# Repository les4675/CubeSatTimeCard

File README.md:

Currently we have developed models from the top level overview of our time card, along with setting up the SOM. Our goal in the next few months is program the SOM to take in data from a GNSS through the CAN protcol and to fine tone the PLL with the atomic clock that we have aquired.

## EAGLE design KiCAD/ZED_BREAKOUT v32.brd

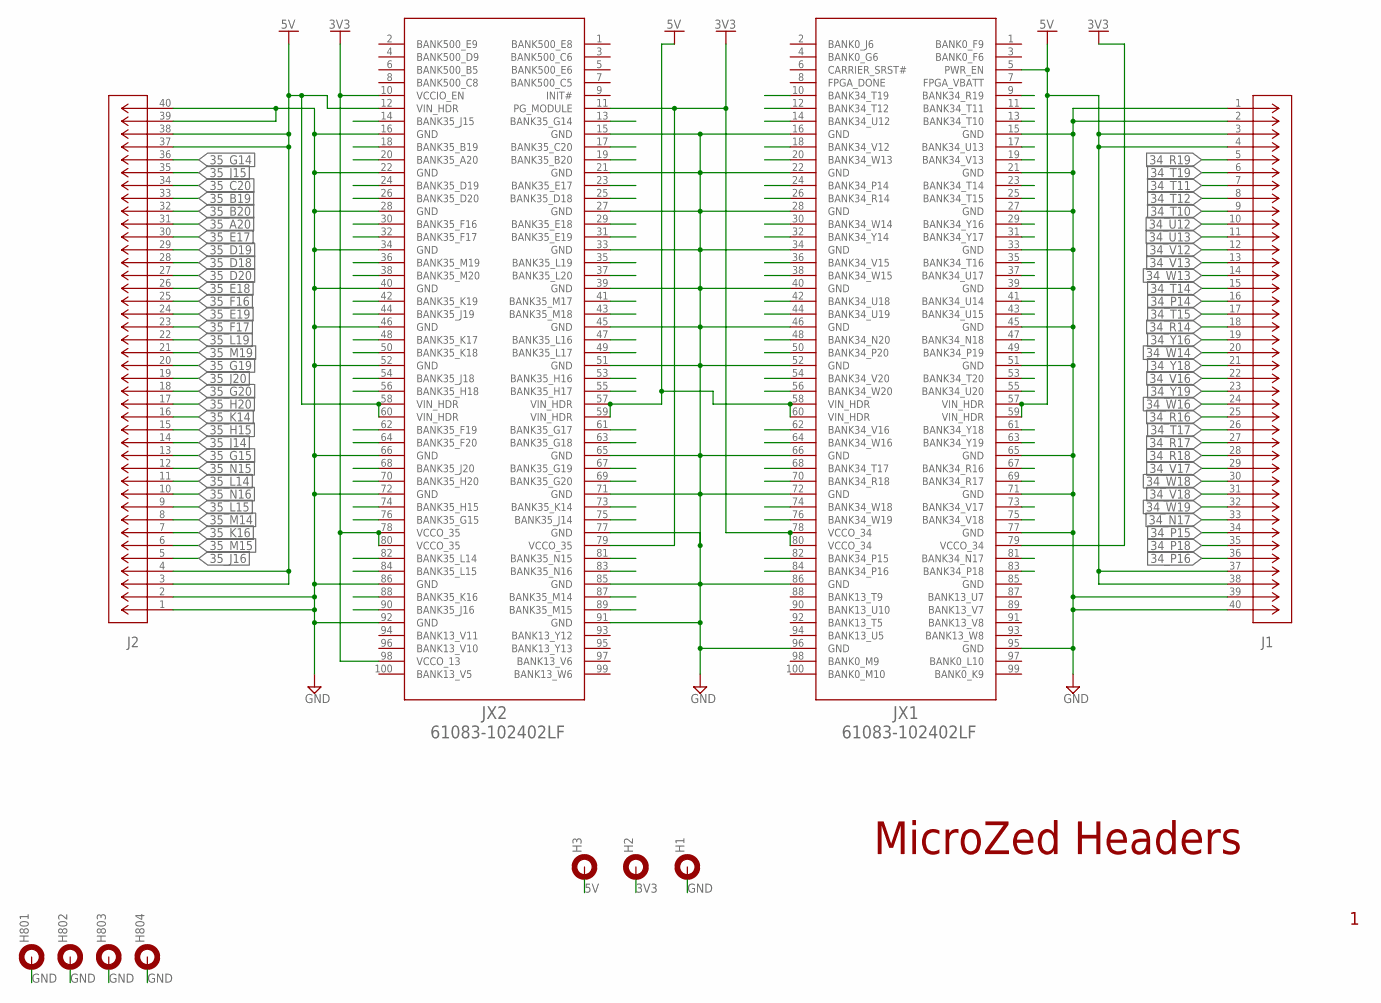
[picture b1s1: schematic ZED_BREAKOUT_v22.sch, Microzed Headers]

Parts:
H1, H2, H3, H801, H802, H803, H804: MOUNT-PAD-ROUND5.0; 5,0-PAD
J1, J2: TD-120-G-AACON40_2X20_TU_HTS_SAI; CON40_2X20_TU_HTS_SAI
JX1, JX2: 61083-102402LF

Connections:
3V3: H2.B5, JX1.78 (VCCO_34), JX1.79 (VCCO_34), JX1.80 (VCCO_34), JX2.10 (VCCIO_EN), JX2.11 (PG_MODULE), JX2.78 (VCCO_35), JX2.79 (VCCO_35), JX2.80 (VCCO_35), JX2.98 (VCCO_13)
5V: H3.B5, J1.3, J1.4, J1.37, J1.38, J2.3, J2.4, J2.37, J2.38, JX1.5 (PWR_EN), JX1.57 (VIN_HDR), JX1.58 (VIN_HDR), JX1.59 (VIN_HDR), JX1.60 (VIN_HDR), JX2.12 (VIN_HDR), JX2.57 (VIN_HDR), JX2.58 (VIN_HDR), JX2.59 (VIN_HDR), JX2.60 (VIN_HDR)
34_N17: J1.33, JX1.81 (BANK34_N17)
34_N18: JX1.47 (BANK34_N18)
34_N20: JX1.48 (BANK34_N20)
34_P14: J1.16, JX1.24 (BANK34_P14)
34_P15: J1.34, JX1.82 (BANK34_P15)
34_P16: J1.36, JX1.84 (BANK34_P16)
34_P18: J1.35, JX1.83 (BANK34_P18)
34_P19: JX1.49 (BANK34_P19)
34_P20: JX1.50 (BANK34_P20)
34_R14: J1.18, JX1.26 (BANK34_R14)
34_R16: J1.25, JX1.67 (BANK34_R16)
34_R17: J1.27, JX1.69 (BANK34_R17)
34_R18: J1.28, JX1.70 (BANK34_R18)
34_R19: J1.5, JX1.9 (BANK34_R19)
34_T10: J1.9, JX1.13 (BANK34_T10)
34_T11: J1.7, JX1.11 (BANK34_T11)
34_T12: J1.8, JX1.12 (BANK34_T12)
34_T14: J1.15, JX1.23 (BANK34_T14)
34_T15: J1.17, JX1.25 (BANK34_T15)
34_T16: JX1.35 (BANK34_T16)
34_T17: J1.26, JX1.68 (BANK34_T17)
34_T19: J1.6, JX1.10 (BANK34_T19)
34_T20: JX1.53 (BANK34_T20)
34_U12: J1.10, JX1.14 (BANK34_U12)
34_U13: J1.11, JX1.17 (BANK34_U13)
34_U14: JX1.41 (BANK34_U14)
34_U15: JX1.43 (BANK34_U15)
34_U17: JX1.37 (BANK34_U17)
34_U18: JX1.42 (BANK34_U18)
34_U19: JX1.44 (BANK34_U19)
34_U20: JX1.55 (BANK34_U20)
34_V12: J1.12, JX1.18 (BANK34_V12)
34_V13: J1.13, JX1.19 (BANK34_V13)
34_V15: JX1.36 (BANK34_V15)
34_V16: J1.22, JX1.62 (BANK34_V16)
34_V17: J1.29, JX1.73 (BANK34_V17)
34_V18: J1.31, JX1.75 (BANK34_V18)
34_V20: JX1.54 (BANK34_V20)
34_W13: J1.14, JX1.20 (BANK34_W13)
34_W14: J1.20, JX1.30 (BANK34_W14)
34_W15: JX1.38 (BANK34_W15)
34_W16: J1.24, JX1.64 (BANK34_W16)
34_W18: J1.30, JX1.74 (BANK34_W18)
34_W19: J1.32, JX1.76 (BANK34_W19)
34_W20: JX1.56 (BANK34_W20)
34_Y14: JX1.32 (BANK34_Y14)
34_Y16: J1.19, JX1.29 (BANK34_Y16)
34_Y17: JX1.31 (BANK34_Y17)
34_Y18: J1.21, JX1.61 (BANK34_Y18)
34_Y19: J1.23, JX1.63 (BANK34_Y19)
35_A20: J2.31, JX2.20 (BANK35_A20)
35_B19: J2.33, JX2.18 (BANK35_B19)
35_B20: J2.32, JX2.19 (BANK35_B20)
35_C20: J2.34, JX2.17 (BANK35_C20)
35_D18: J2.28, JX2.25 (BANK35_D18)
35_D19: J2.29, JX2.24 (BANK35_D19)
35_D20: J2.27, JX2.26 (BANK35_D20)
35_E17: J2.30, JX2.23 (BANK35_E17)
35_E18: J2.26, JX2.29 (BANK35_E18)
35_E19: J2.24, JX2.31 (BANK35_E19)
35_F16: J2.25, JX2.30 (BANK35_F16)
35_F17: J2.23, JX2.32 (BANK35_F17)
35_F19: JX2.62 (BANK35_F19)
35_F20: JX2.64 (BANK35_F20)
35_G14: J2.36, JX2.13 (BANK35_G14)
35_G15: J2.13, JX2.76 (BANK35_G15)
35_G17: JX2.61 (BANK35_G17)
35_G18: JX2.63 (BANK35_G18)
35_G19: J2.20, JX2.67 (BANK35_G19)
35_G20: J2.18, JX2.69 (BANK35_G20)
35_H15: J2.15, JX2.74 (BANK35_H15)
35_H16: JX2.53 (BANK35_H16)
35_H17: JX2.55 (BANK35_H17)
35_H18: JX2.56 (BANK35_H18)
35_H20: J2.17, JX2.70 (BANK35_H20)
35_J14: J2.14, JX2.75 (BANK35_J14)
35_J15: J2.35, JX2.14 (BANK35_J15)
35_J16: J2.5, JX2.90 (BANK35_J16)
35_J18: JX2.54 (BANK35_J18)
35_J19: JX2.44 (BANK35_J19)
35_J20: J2.19, JX2.68 (BANK35_J20)
35_K14: J2.16, JX2.73 (BANK35_K14)
35_K16: J2.7, JX2.88 (BANK35_K16)
35_K17: JX2.48 (BANK35_K17)
35_K18: JX2.50 (BANK35_K18)
35_K19: JX2.42 (BANK35_K19)
35_L14: J2.11, JX2.82 (BANK35_L14)
35_L15: J2.9, JX2.84 (BANK35_L15)
35_L16: JX2.47 (BANK35_L16)
35_L17: JX2.49 (BANK35_L17)
35_L19: J2.22, JX2.35 (BANK35_L19)
35_L20: JX2.37 (BANK35_L20)
35_M14: J2.8, JX2.87 (BANK35_M14)
35_M15: J2.6, JX2.89 (BANK35_M15)
35_M17: JX2.41 (BANK35_M17)
35_M18: JX2.43 (BANK35_M18)
35_M19: J2.21, JX2.36 (BANK35_M19)
35_M20: JX2.38 (BANK35_M20)
35_N15: J2.12, JX2.81 (BANK35_N15)
35_N16: J2.10, JX2.83 (BANK35_N16)
GND: H1.B5, H801.B5, H802.B5, H803.B5, H804.B5, J1.1, J1.2, J1.39, J1.40, J2.1, J2.2, J2.39, J2.40, JX1.15 (GND), JX1.16 (GND), JX1.21 (GND), JX1.22 (GND), JX1.27 (GND), JX1.28 (GND), JX1.33 (GND), JX1.34 (GND), JX1.39 (GND), JX1.40 (GND), JX1.45 (GND), JX1.46 (GND), JX1.51 (GND), JX1.52 (GND), JX1.65 (GND), JX1.66 (GND), JX1.71 (GND), JX1.72 (GND), JX1.77 (GND), JX1.86 (GND), JX1.95 (GND), JX1.96 (GND), JX2.15 (GND), JX2.16 (GND), JX2.21 (GND), JX2.22 (GND), JX2.27 (GND), JX2.28 (GND), JX2.33 (GND), JX2.34 (GND), JX2.39 (GND), JX2.40 (GND), JX2.45 (GND), JX2.46 (GND), JX2.51 (GND), JX2.52 (GND), JX2.65 (GND), JX2.66 (GND), JX2.71 (GND), JX2.72 (GND), JX2.77 (GND), JX2.85 (GND), JX2.86 (GND), JX2.91 (GND), JX2.92 (GND)

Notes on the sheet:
MicroZed Headers

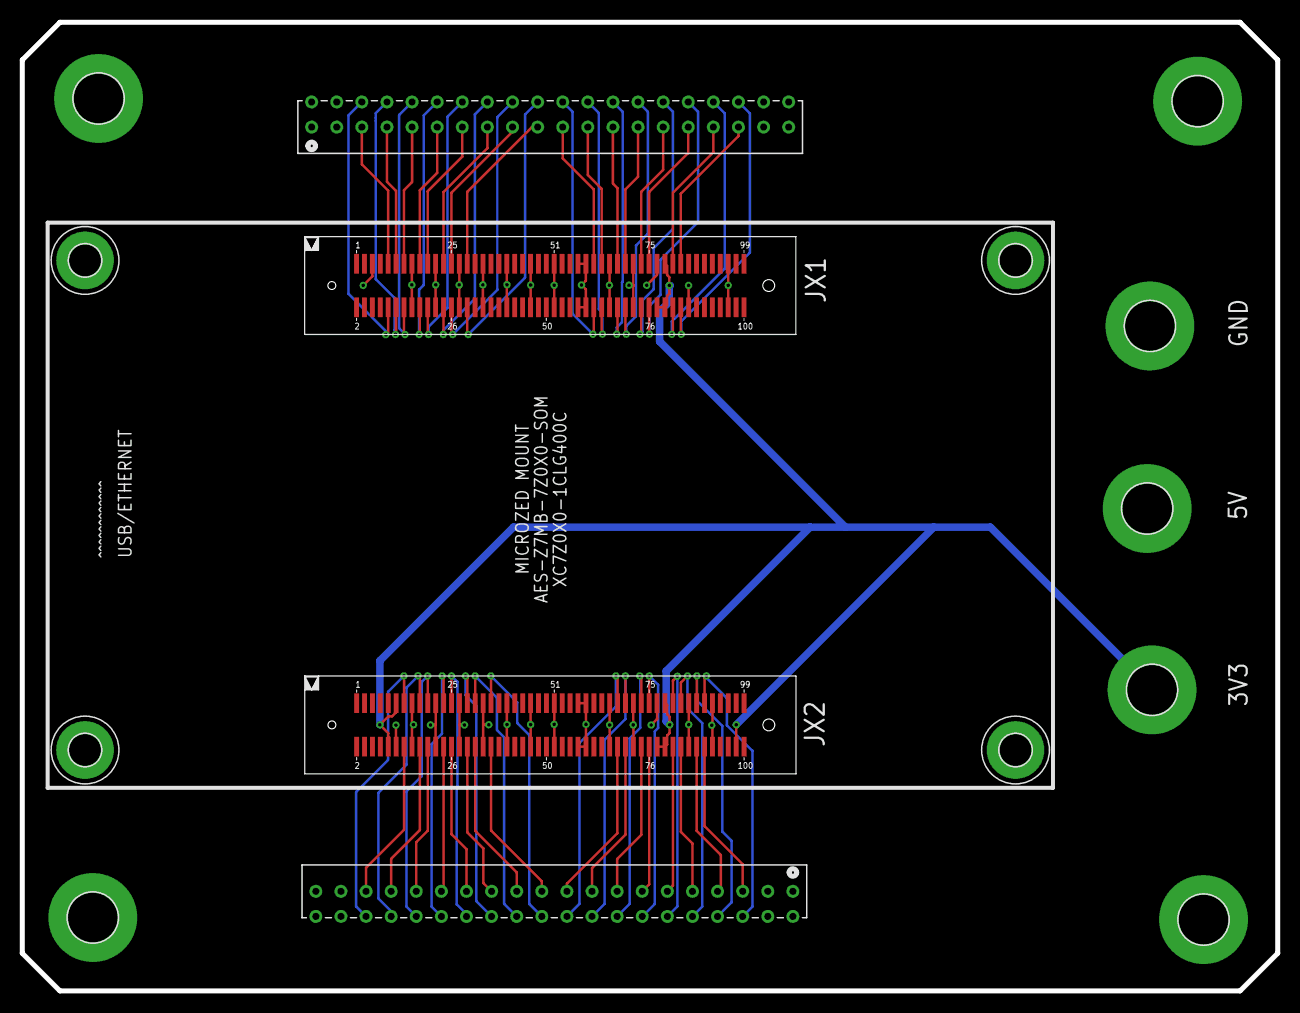
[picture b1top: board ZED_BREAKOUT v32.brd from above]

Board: 4 copper layers, 127.0 x 98.0 mm, 15 parts (0 on the bottom side), 67 nets.

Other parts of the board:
E$1, E$2, E$3, E$4: 3,2-PAD

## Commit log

2024-10-24 create vivado directory
2024-10-24 High Level Model
2024-10-24 Added GNSS?
2024-10-29 Matlab Model Update
2024-10-31 Sim Model
2024-10-31 help
2024-10-31 Model Done?
2024-11-01 Added some notes for user understanding
2024-11-21 Started development on a realistic oscillator block
2024-11-21 End of day 11-21-2024
2024-11-26 Added temperature profile for sattilite in orbit
2024-11-26 Added MATLAB model for testing how to implement transient allan deviation
2024-11-26 Please enter the commit message for your changes. Lines starting end of day end of da
2024-11-29 SHould actually save temperature model addition
2024-11-30 End of day 11-29-2024
2024-12-03 Beginning of day, added phase discriminator
2024-12-03 end of day
2024-12-09 init
2024-12-09 README
2025-01-02 Create LICENSE
2025-01-06 Documentation update
2025-01-16 logging functionallity
2025-01-28 Implemented PID Filter simulation. Read annotations.
2025-01-30 Updated after meeting with Stephan
2025-02-06 BME688 I2C Driver
2025-02-06 Drivers :)
2025-02-06 Added a matlab script that will help me determing the power spectrum of oscillator noise
2025-02-07 repeat
2025-02-11 Obtained transfer function for oscillator noise power spectrum due to allan deviation related effects
2025-02-11 Decreased size of ADEV_Data.mat
2025-02-11 Deleted ADEV_Data. Still trying to push
2025-02-18 From MSD Computer sims
2025-02-20 Working model for noise generator that creates proper ADEV curve
2025-02-20 commit before merge
2025-02-23 Phase Detector Testbench
2025-02-24 Moved figures into a folder
2025-02-25 Added KiCAD Files
2025-02-26 Schematic Progress. Added connections to the MicroZed and added a 3v3 rail regulator
2025-02-27 More Schematic Updates
    Added power monitors and connectors, along with finishing the power circuitry.
2025-02-27 Schematic should be finished, onto layout
2025-02-27 Assignmed Most footprints. Created footprints for oscillators.
2025-02-28 Started layout
2025-03-01 Finished Component Placement and Arrangement.
2025-03-01 Routed Breakouts
2025-03-01 A lot of routing progress done
2025-03-03 Power Pours
2025-03-03 EOD
    Nearly finished routing
2025-03-04 Routing progress
2025-03-04 DONE ROUTINGgit add .git add .
2025-03-04 Re-commit, this means nothing
2025-03-04 Done with routing-related DRCs!!
2025-03-04 Almost done silkscreening :,)
2025-03-04 NO DRC ERRORS!!!!
    Fuck I'm tired
2025-03-04 Done :D
    Existence is pain
2025-03-04 Added notes from review with Carlos
2025-03-04 Started BOM
2025-03-04 Part numbers added to BOM
    the .xlsx file
2025-03-05 Finished Edits
    Edits from design review are done, and the BOM has part numbers filled out
2025-03-06 Output Files Generated
2025-03-10 Redid MSP430 Test Code
2025-03-11 Currently Logging Data
2025-03-14 Processed Some Data
    From the 72hr dataset
2025-03-14 Started Excel Curve Fitting
2025-03-15 Compiled Data
    From 104 Hour Test
2025-03-16 Done data processing for now
2025-03-18 Added Simulink data processing method
2025-03-23 Added CCS Project to use MSP430FR2355
    as new, more precise phase detector

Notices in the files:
parts and their libraries:
COPYRIGHT: Copyright (C) 2024 Ultra Librarian. All rights reserved.
